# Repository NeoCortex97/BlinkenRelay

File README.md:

# BlinkenRelay
A project to have cheap and simple control over 24V Outputs

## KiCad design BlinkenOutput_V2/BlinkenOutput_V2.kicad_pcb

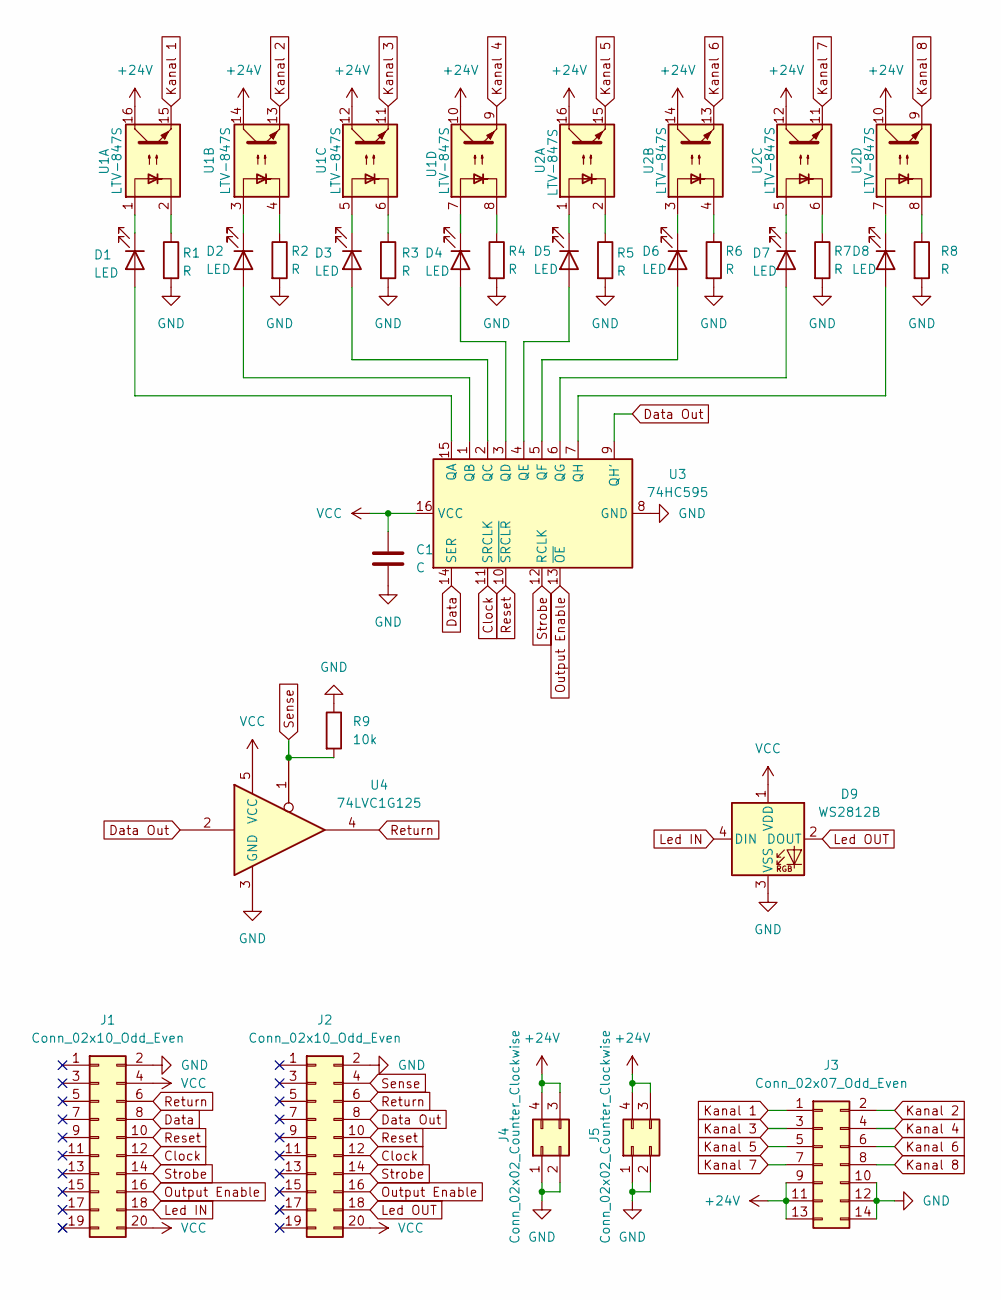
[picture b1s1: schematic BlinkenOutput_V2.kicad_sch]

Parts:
C1: C; C_0805_2012Metric_Pad1.18x1.45mm_HandSolder
D1, D2, D3, D4, D5, D6, D7, D8: LED; LED_0805_2012Metric_Pad1.15x1.40mm_HandSolder
D9: WS2812B; LED_WS2812B_PLCC4_5.0x5.0mm_P3.2mm
J1: Conn_02x10_Odd_Even; PinSocket_2x10_P2.54mm_Vertical_SMD
J2: Conn_02x10_Odd_Even; PinHeader_2x10_P2.54mm_Vertical_SMD
J3: Conn_02x07_Odd_Even; IDC-Header_2x07_P2.54mm_Horizontal
J4: Conn_02x02_Counter_Clockwise; PinHeader_2x02_P2.54mm_Vertical_SMD
J5: Conn_02x02_Counter_Clockwise; PinSocket_2x02_P2.54mm_Vertical_SMD
R1, R2, R3, R4, R5, R6, R7, R8: R; R_0805_2012Metric_Pad1.20x1.40mm_HandSolder
R9: 10k; R_0805_2012Metric_Pad1.20x1.40mm_HandSolder
U1, U2: LTV-847S; SMDIP-16_W9.53mm
U3: 74HC595; SO-16_3.9x9.9mm_P1.27mm
U4: 74LVC1G125; SOT-23-5_HandSoldering

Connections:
+24V: J3.9, J3.11, J3.13, J4.3, J4.4, J5.3, J5.4, U1.10, U1.12, U1.14, U1.16, U2.10, U2.12, U2.14, U2.16
Clock: J1.12, J2.12, U3.11 (SRCLK)
Data: J1.8, U3.14 (SER)
Data Out: J2.8, U3.9 (QH'), U4.2
GND: C1.2, D9.3 (VSS), J1.2, J2.2, J3.10, J3.12, J3.14, J4.1, J4.2, J5.1, J5.2, R1.2, R2.2, R3.2, R4.2, R5.2, R6.2, R7.2, R8.2, R9.1, U3.8 (GND), U4.3 (GND)
Kanal 1: J3.1, U1.15
Kanal 2: J3.2, U1.13
Kanal 3: J3.3, U1.11
Kanal 4: J3.4, U1.9
Kanal 5: J3.5, U2.15
Kanal 6: J3.6, U2.13
Kanal 7: J3.7, U2.11
Kanal 8: J3.8, U2.9
Led IN: D9.4 (DIN), J1.18
Led OUT: D9.2 (DOUT), J2.18
unnamed: D1.2 (A), U3.15 (QA)
unnamed: D1.1 (K), U1.1
unnamed: D2.2 (A), U3.1 (QB)
unnamed: D2.1 (K), U1.3
unnamed: D3.2 (A), U3.2 (QC)
unnamed: D3.1 (K), U1.5
unnamed: D4.2 (A), U3.3 (QD)
unnamed: D4.1 (K), U1.7
unnamed: D5.2 (A), U3.4 (QE)
unnamed: D5.1 (K), U2.1
unnamed: D6.2 (A), U3.5 (QF)
unnamed: D6.1 (K), U2.3
unnamed: D7.2 (A), U3.6 (QG)
unnamed: D7.1 (K), U2.5
unnamed: D8.2 (A), U3.7 (QH)
unnamed: D8.1 (K), U2.7
unnamed: R1.1, U1.2
unnamed: R2.1, U1.4
unnamed: R3.1, U1.6
unnamed: R4.1, U1.8
unnamed: R5.1, U2.2
unnamed: R6.1, U2.4
unnamed: R7.1, U2.6
unnamed: R8.1, U2.8
Output Enable: J1.16, J2.16, U3.13 (~OE)
Reset: J1.10, J2.10, U3.10 (~SRCLR)
Return: J1.6, J2.6, U4.4
Sense: J2.4, R9.2, U4.1
Strobe: J1.14, J2.14, U3.12 (RCLK)
VCC: C1.1, D9.1 (VDD), J1.4, J1.20, J2.20, U3.16 (VCC), U4.5 (VCC)

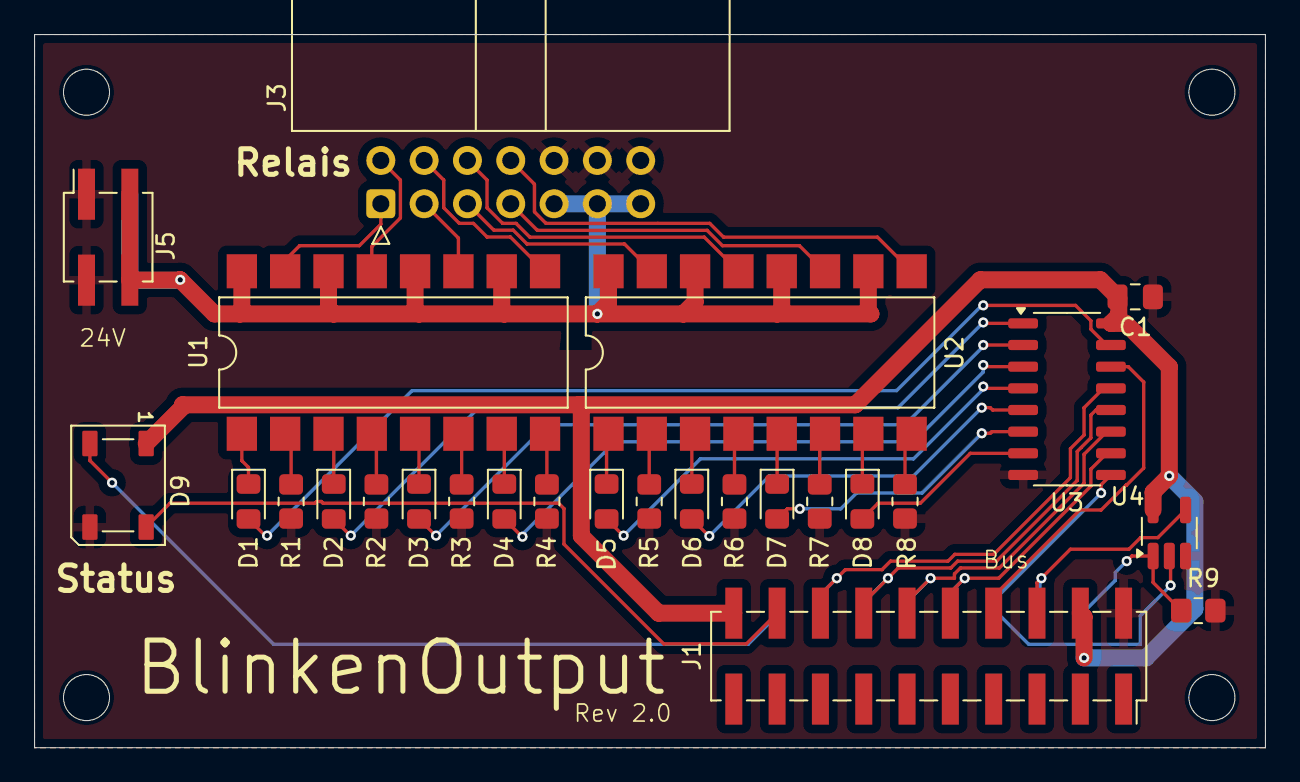
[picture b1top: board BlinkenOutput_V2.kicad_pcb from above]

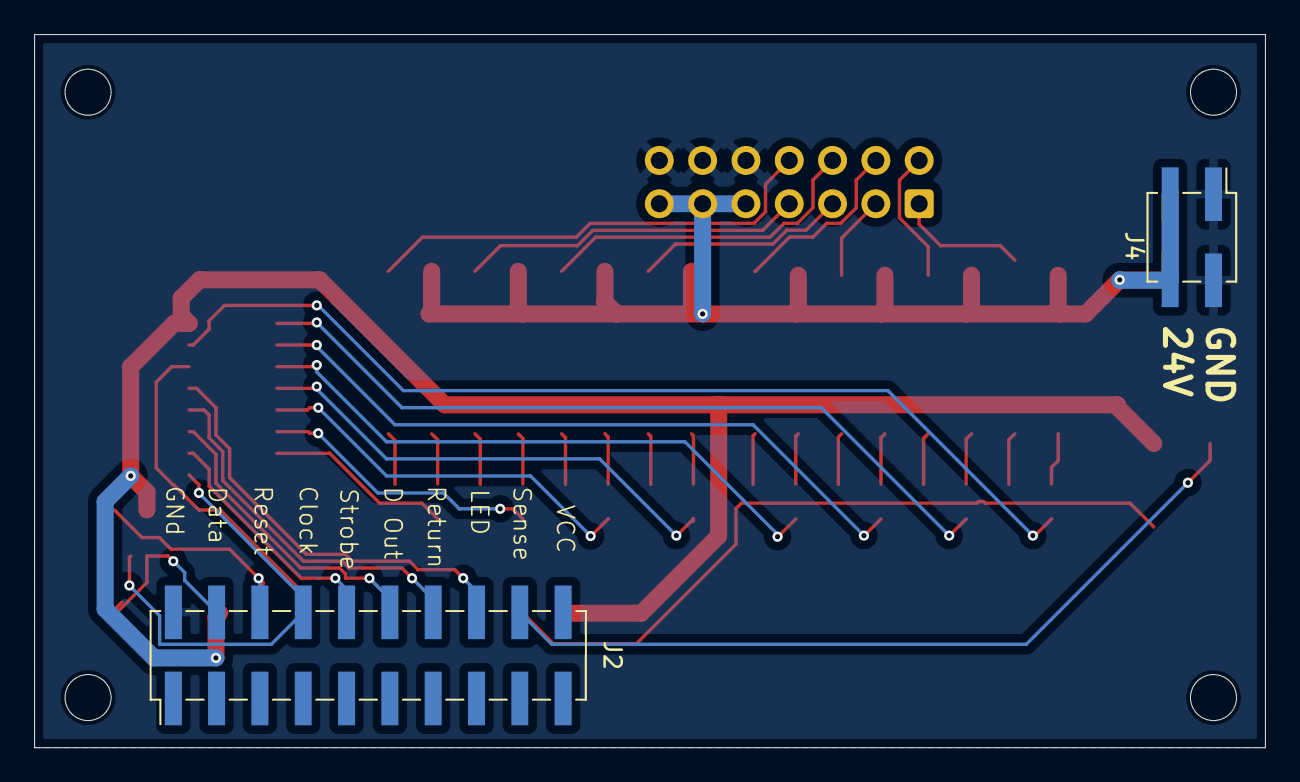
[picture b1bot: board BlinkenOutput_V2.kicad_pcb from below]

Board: 2 copper layers, 72.2 x 41.8 mm, 28 parts (2 on the bottom side), 45 nets.

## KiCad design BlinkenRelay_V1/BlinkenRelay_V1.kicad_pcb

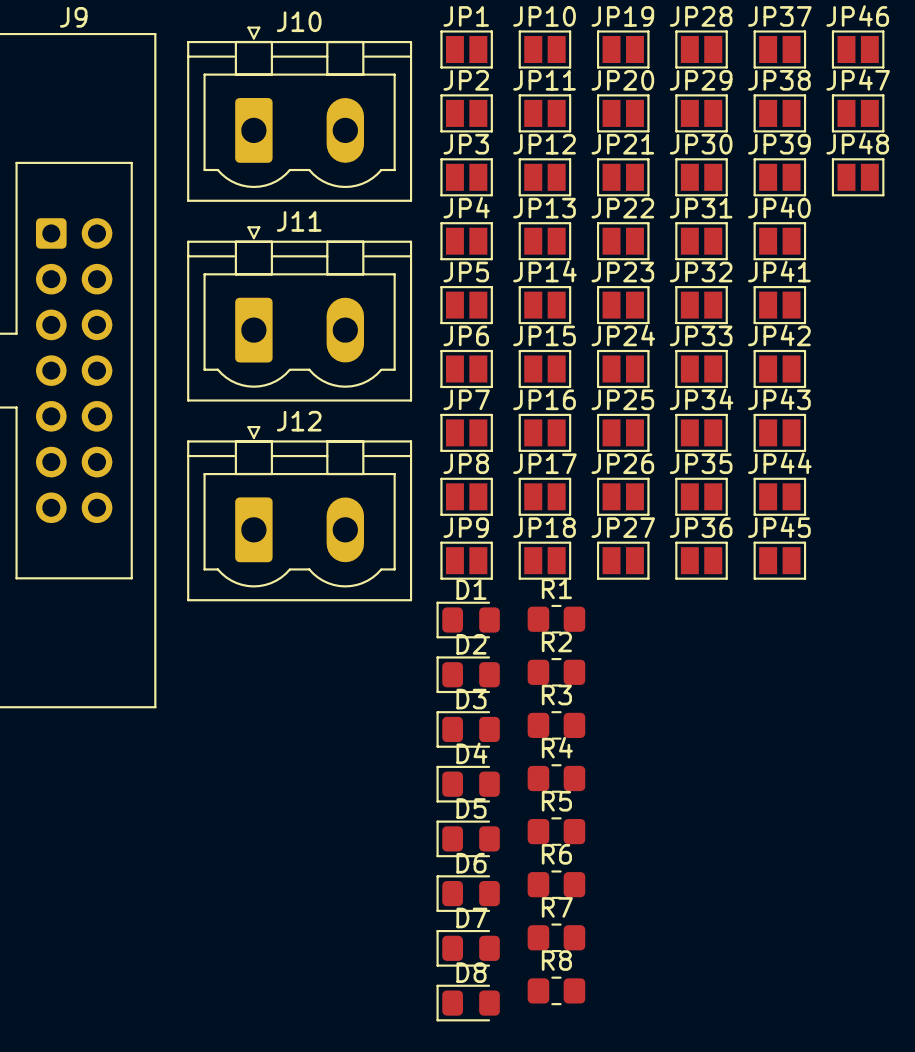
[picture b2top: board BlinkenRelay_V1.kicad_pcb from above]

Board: 2 copper layers, 68 parts (0 on the bottom side), 44 nets, no tracks yet.

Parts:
D1, D2, D3, D4, D5, D6, D7, D8: LED Low current; LED_0805_2012Metric_Pad1.15x1.40mm_HandSolder
J9: Conn_02x07_Odd_Even; IDC-Header_2x07_P2.54mm_Latch_Vertical
J10, J11, J12: Conn_01x02_Socket; PhoenixContact_MSTBVA_2,5_2-G-5,08_1x02_P5.08mm_Vertical
JP1, JP2, JP3, JP4, JP5, JP6, JP7, JP8, JP9, JP10, JP11, JP12, JP13, JP14, JP15, JP16, JP17, JP18, JP19, JP20, JP21, JP22, JP23, JP24, JP25, JP26, JP27, JP28, JP29, JP30, JP31, JP32, JP33, JP34, JP35, JP36, JP37, JP38, JP39, JP40, JP41, JP42, JP43, JP44, JP45, JP46, JP47, JP48: Jumper_2_Open; SolderJumper-2_P1.3mm_Open_Pad1.0x1.5mm
R1, R2, R3, R4, R5, R6, R7, R8: 12.1k; R_0805_2012Metric_Pad1.20x1.40mm_HandSolder

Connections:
+24V: J9.9, J9.11, J9.13, J10.1
GND: J9.10, J9.12, J9.14, J10.2, R1.2, R2.2, R3.2, R4.2, R5.2, R6.2, R7.2, R8.2
K1_COM: JP1.2 (B), JP2.2 (B)
K1_NC: JP5.2 (B), JP6.2 (B)
K1_NO: JP3.2 (B), JP4.2 (B)
K2_COM: JP7.2 (B), JP8.2 (B)
K2_NC: JP10.2 (B), JP12.2 (B)
K2_NO: JP9.2 (B), JP11.2 (B)
K3_COM: JP13.2 (B), JP14.2 (B)
K3_NC: JP16.2 (B), JP18.2 (B)
K3_NO: JP15.2 (B), JP17.2 (B)
K4_COM: JP19.2 (B), JP20.2 (B)
K4_NC: JP22.2 (B), JP24.2 (B)
K4_NO: JP21.2 (B), JP23.2 (B)
K5_COM: JP25.2 (B), JP26.2 (B)
K5_NC: JP28.2 (B), JP30.2 (B)
K5_NO: JP27.2 (B), JP29.2 (B)
K6_COM: JP31.2 (B), JP32.2 (B)
K6_NC: JP34.2 (B), JP36.2 (B)
K6_NO: JP33.2 (B), JP35.2 (B)
K7_COM: JP37.2 (B), JP38.2 (B)
K7_NC: JP40.2 (B), JP42.2 (B)
K7_NO: JP39.2 (B), JP41.2 (B)
K8_COM: JP43.2 (B), JP44.2 (B)
K8_NC: JP46.2 (B), JP48.2 (B)
K8_NO: JP45.2 (B), JP47.2 (B)
Kanal 1: D1.1 (K), J9.1
Kanal 2: D2.1 (K), J9.2
Kanal 3: D3.1 (K), J9.3
Kanal 4: D4.1 (K), J9.4
Kanal 5: D5.1 (K), J9.5
Kanal 6: D6.1 (K), J9.6
Kanal 7: D7.1 (K), J9.7
Kanal 8: D8.1 (K), J9.8
unnamed: D1.2 (A), R1.1
unnamed: D2.2 (A), R2.1
unnamed: D3.2 (A), R3.1
unnamed: D4.2 (A), R4.1
unnamed: D5.2 (A), R5.1
unnamed: D6.2 (A), R6.1
unnamed: D7.2 (A), R7.1
unnamed: D8.2 (A), R8.1
Rail A: J11.1, J12.1, JP2.1 (A), JP3.1 (A), JP5.1 (A), JP7.1 (A), JP9.1 (A), JP10.1 (A), JP13.1 (A), JP15.1 (A), JP16.1 (A), JP19.1 (A), JP21.1 (A), JP22.1 (A), JP25.1 (A), JP27.1 (A), JP28.1 (A), JP31.1 (A), JP33.1 (A), JP34.1 (A), JP37.1 (A), JP39.1 (A), JP40.1 (A), JP43.1 (A), JP45.1 (A), JP46.1 (A)
Rail B: J11.2, J12.2, JP1.1 (A), JP4.1 (A), JP6.1 (A), JP8.1 (A), JP11.1 (A), JP12.1 (A), JP14.1 (A), JP17.1 (A), JP18.1 (A), JP20.1 (A), JP23.1 (A), JP24.1 (A), JP26.1 (A), JP29.1 (A), JP30.1 (A), JP32.1 (A), JP35.1 (A), JP36.1 (A), JP38.1 (A), JP41.1 (A), JP42.1 (A), JP44.1 (A), JP47.1 (A), JP48.1 (A)

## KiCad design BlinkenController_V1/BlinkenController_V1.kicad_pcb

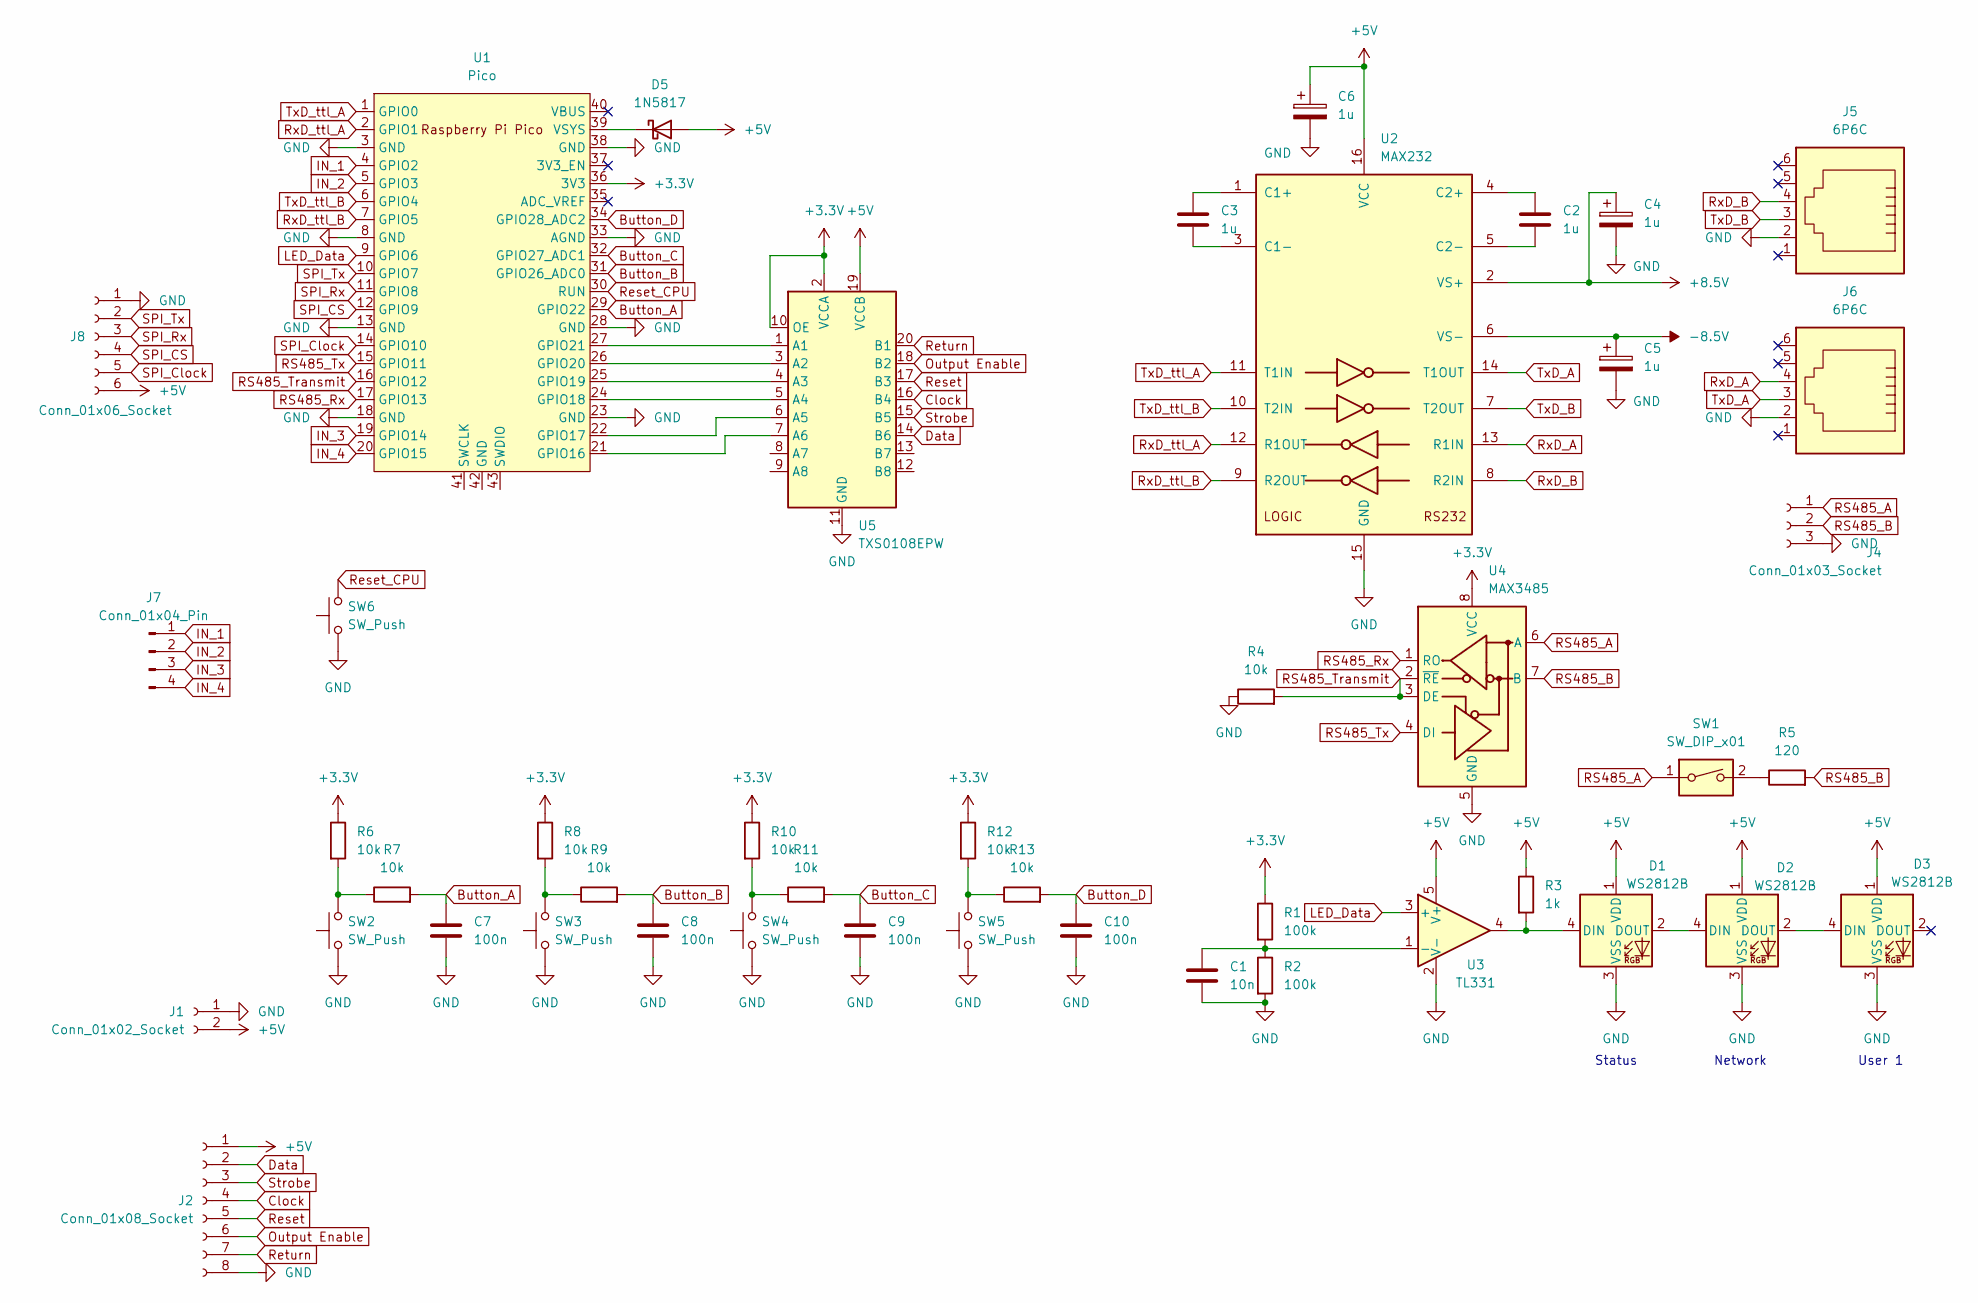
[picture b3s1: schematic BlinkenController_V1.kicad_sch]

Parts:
C1: 10n; C_0805_2012Metric_Pad1.18x1.45mm_HandSolder
C2, C3: 1u; C_Disc_D5.0mm_W2.5mm_P5.00mm
C4, C5, C6: 1u; C_Radial_D6.3mm_H5.0mm_P2.50mm
C7, C8, C9, C10: 100n; C_0805_2012Metric_Pad1.18x1.45mm_HandSolder
D1, D2, D3: WS2812B; LED_WS2812B_PLCC4_5.0x5.0mm_P3.2mm
D5: 1N5817; D_DO-41_SOD81_P10.16mm_Horizontal
J1: Conn_01x02_Socket; PhoenixContact_MSTBVA_2,5_2-G_1x02_P5.00mm_Vertical
J2: Conn_01x08_Socket; PinSocket_1x08_P2.54mm_Horizontal
J4: Conn_01x03_Socket; PhoenixContact_MSTBVA_2,5_3-G_1x03_P5.00mm_Vertical
J5, J6: 6P6C; RJ12_Amphenol_54601-x06_Horizontal
J7: Conn_01x04_Pin; PhoenixContact_MSTBVA_2,5_4-G_1x04_P5.00mm_Vertical
J8: Conn_01x06_Socket; PinSocket_1x06_P2.54mm_Vertical
R1, R2: 100k; R_0805_2012Metric_Pad1.20x1.40mm_HandSolder
R3: 1k; R_0805_2012Metric_Pad1.20x1.40mm_HandSolder
R4, R6, R7, R8, R9, R10, R11, R12, R13: 10k; R_0805_2012Metric_Pad1.20x1.40mm_HandSolder
R5: 120; R_0805_2012Metric_Pad1.20x1.40mm_HandSolder
SW1: SW_DIP_x01; SW_Slide-03_Wuerth-WS-SLTV_10x2.5x6.4_P2.54mm
SW2, SW3, SW4, SW5, SW6: SW_Push; SW_Tactile_SPST_NO_Straight_CK_PTS636Sx25SMTRLFS
U1: Pico; RaspberryPi_Pico_W_SMD
U2: MAX232; DIP-16_W7.62mm_LongPads
U3: TL331; SOT-23-5
U4: MAX3485; SOIC-8_3.9x4.9mm_P1.27mm
U5: TXS0108EPW; TSSOP-20_4.4x6.5mm_P0.65mm

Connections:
+3.3V: R1.1, R6.1, R8.1, R10.1, R12.1, U1.36 (3V3), U4.8 (VCC), U5.2 (VCCA), U5.10 (OE)
+5V: C6.1, D1.1 (VDD), D2.1 (VDD), D3.1 (VDD), D5.2 (A), J1.2, J2.1, J8.6, R3.1, U2.16 (VCC), U3.5 (V+), U5.19 (VCCB)
+8.5V: C4.1, U2.2 (VS+)
-8.5V: C5.1, U2.6 (VS-)
Button_A: C7.1, R7.2, U1.29 (GPIO22)
Button_B: C8.1, R9.2, U1.31 (GPIO26_ADC0)
Button_C: C9.1, R11.2, U1.32 (GPIO27_ADC1)
Button_D: C10.1, R13.2, U1.34 (GPIO28_ADC2)
Clock: J2.4, U1.24 (GPIO18), U5.5 (A4), U5.16 (B4)
Data: J2.2, U1.21 (GPIO16), U5.7 (A6), U5.14 (B6)
GND: C1.2, C4.2, C5.2, C6.2, C7.2, C8.2, C9.2, C10.2, D1.3 (VSS), D2.3 (VSS), D3.3 (VSS), J1.1, J2.8, J4.3, J5.2, J6.2, J8.1, R2.2, R4.1, SW2.1, SW3.1, SW4.1, SW5.1, SW6.1, U1.3 (GND), U1.8 (GND), U1.13 (GND), U1.18 (GND), U1.23 (GND), U1.28 (GND), U1.33 (AGND), U1.38 (GND), U2.15 (GND), U3.2 (V-), U4.5 (GND), U5.11 (GND)
IN_1: J7.1, U1.4 (GPIO2)
IN_2: J7.2, U1.5 (GPIO3)
IN_3: J7.3, U1.19 (GPIO14)
IN_4: J7.4, U1.20 (GPIO15)
LED_Data: U1.9 (GPIO6), U3.3 (+)
unnamed: D1.4 (DIN), R3.2, U3.4
unnamed: D1.2 (DOUT), D2.4 (DIN)
unnamed: D2.2 (DOUT), D3.4 (DIN)
unnamed: D5.1 (K), U1.39 (VSYS)
unnamed: R5.1, SW1.2
unnamed: R6.2, R7.1, SW2.2
unnamed: R8.2, R9.1, SW3.2
unnamed: R10.2, R11.1, SW4.2
unnamed: R12.2, R13.1, SW5.2
unnamed: C3.1, U2.1 (C1+)
unnamed: C3.2, U2.3 (C1-)
unnamed: C2.1, U2.4 (C2+)
unnamed: C2.2, U2.5 (C2-)
unnamed: C1.1, R1.2, R2.1, U3.1 (-)
Output Enable: J2.6, U1.26 (GPIO20), U5.3 (A2), U5.18 (B2)
RS485_A: J4.1, SW1.1, U4.6 (A)
RS485_B: J4.2, R5.2, U4.7 (B)
RS485_Rx: U1.17 (GPIO13), U4.1 (RO)
RS485_Transmit: R4.2, U1.16 (GPIO12), U4.2 (~RE), U4.3 (DE)
RS485_Tx: U1.15 (GPIO11), U4.4 (DI)
Reset: J2.5, U1.25 (GPIO19), U5.4 (A3), U5.17 (B3)
Reset_CPU: SW6.2, U1.30 (RUN)
Return: J2.7, U1.27 (GPIO21), U5.1 (A1), U5.20 (B1)
RxD_A: J6.4, U2.13 (R1IN)
RxD_B: J5.4, U2.8 (R2IN)
RxD_ttl_A: U1.2 (GPIO1), U2.12 (R1OUT)
RxD_ttl_B: U1.7 (GPIO5), U2.9 (R2OUT)
SPI_CS: J8.4, U1.12 (GPIO9)
SPI_Clock: J8.5, U1.14 (GPIO10)
SPI_Rx: J8.3, U1.11 (GPIO8)
SPI_Tx: J8.2, U1.10 (GPIO7)
Strobe: J2.3, U1.22 (GPIO17), U5.6 (A5), U5.15 (B5)
TxD_A: J6.3, U2.14 (T1OUT)
TxD_B: J5.3, U2.7 (T2OUT)
TxD_ttl_A: U1.1 (GPIO0), U2.11 (T1IN)
TxD_ttl_B: U1.6 (GPIO4), U2.10 (T2IN)

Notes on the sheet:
Network
User 1
Status

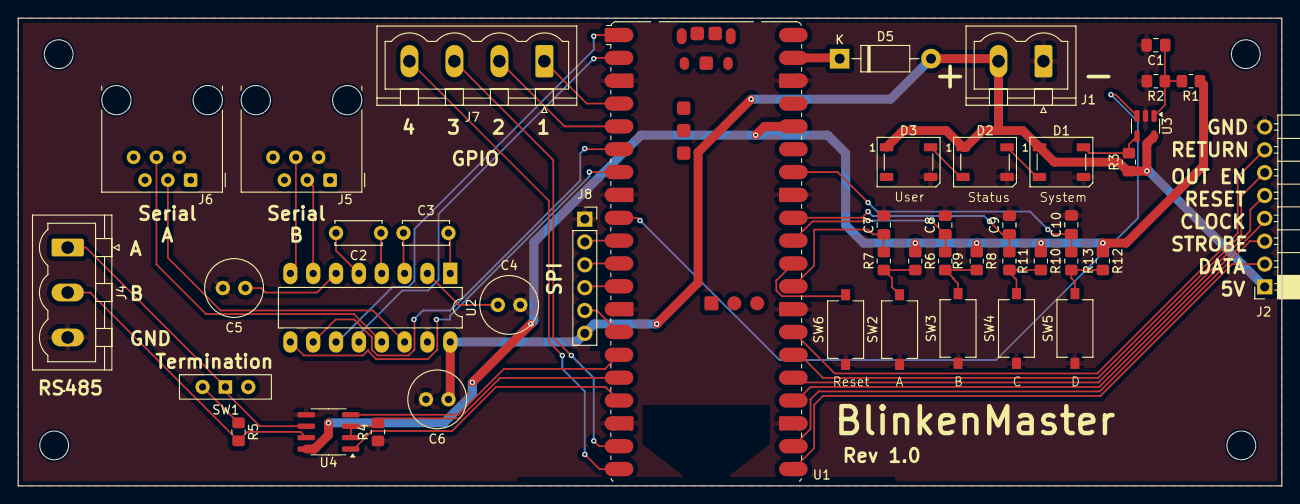
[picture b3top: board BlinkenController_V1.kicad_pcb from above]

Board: 2 copper layers, 140.5 x 52.0 mm, 44 parts (0 on the bottom side), 52 nets.

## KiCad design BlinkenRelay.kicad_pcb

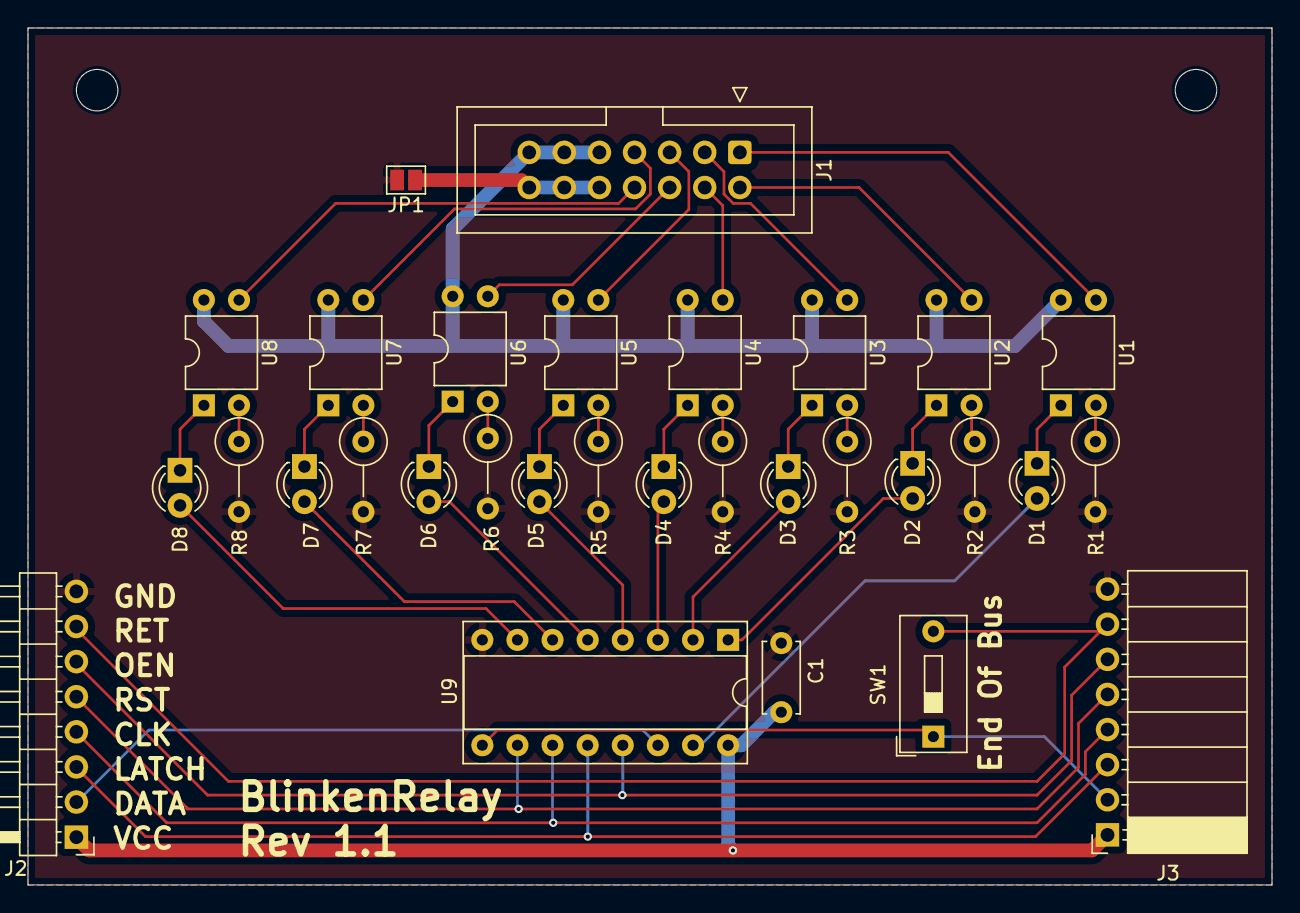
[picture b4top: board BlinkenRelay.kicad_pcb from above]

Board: 2 copper layers, 90.0 x 62.0 mm, 31 parts (0 on the bottom side), 43 nets.

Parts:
C1: 10n; C_Disc_D5.0mm_W2.5mm_P5.00mm
D1, D2, D3, D4, D5, D6, D7, D8: LED; LED_D3.0mm
J1: Conn_02x07_Odd_Even; IDC-Header_2x07_P2.54mm_Vertical
J2: Conn_01x08_Pin; PinHeader_1x08_P2.54mm_Horizontal
J3: Conn_01x08_Socket; PinSocket_1x08_P2.54mm_Horizontal
JP1: Jumper_2_Open; SolderJumper-2_P1.3mm_Open_Pad1.0x1.5mm
R1, R2, R3, R4, R5, R6, R7, R8: 140; R_Axial_DIN0309_L9.0mm_D3.2mm_P5.08mm_Vertical
SW1: SW_DIP_x01; SW_DIP_SPSTx01_Slide_9.78x4.72mm_W7.62mm_P2.54mm
U1, U2, U3, U4, U5, U6, U7, U8: LTV-817; DIP-4_W7.62mm
U9: 74HC595; DIP-16_W7.62mm_Socket

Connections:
+24V: J1.9, J1.11, J1.13, U1.4, U2.4, U3.4, U4.4, U5.4, U6.4, U7.4, U8.4
Clock: J2.4, J3.4, U9.11 (SRCLK)
Data: J2.2, U9.14 (SER)
Data Out: J3.2, SW1.1, U9.9 (QH')
GND: C1.2, J2.8, J3.8, JP1.2 (B), R1.2, R2.2, R3.2, R4.2, R5.2, R6.2, R7.2, R8.2, U9.8 (GND)
Kanal 1: J1.1, U1.3
Kanal 2: J1.2, U2.3
Kanal 3: J1.3, U3.3
Kanal 4: J1.4, U4.3
Kanal 5: J1.5, U5.3
Kanal 6: J1.6, U6.3
Kanal 7: J1.7, U7.3
Kanal 8: J1.8, U8.3
unnamed: D1.2 (A), U9.15 (QA)
unnamed: D1.1 (K), U1.1
unnamed: D2.2 (A), U9.1 (QB)
unnamed: D2.1 (K), U2.1
unnamed: D3.2 (A), U9.2 (QC)
unnamed: D3.1 (K), U3.1
unnamed: D4.2 (A), U9.3 (QD)
unnamed: D4.1 (K), U4.1
unnamed: D5.2 (A), U9.4 (QE)
unnamed: D5.1 (K), U5.1
unnamed: D6.2 (A), U9.5 (QF)
unnamed: D6.1 (K), U6.1
unnamed: D7.2 (A), U9.6 (QG)
unnamed: D7.1 (K), U7.1
unnamed: D8.2 (A), U9.7 (QH)
unnamed: D8.1 (K), U8.1
unnamed: J1.10, J1.12, J1.14, JP1.1 (A)
unnamed: R1.1, U1.2
unnamed: R2.1, U2.2
unnamed: R3.1, U3.2
unnamed: R4.1, U4.2
unnamed: R5.1, U5.2
unnamed: R6.1, U6.2
unnamed: R7.1, U7.2
unnamed: R8.1, U8.2
Output Enable: J2.6, J3.6, U9.13 (~OE)
Reset: J2.5, J3.5, U9.10 (~SRCLR)
Return: J2.7, J3.7, SW1.2
Strobe: J2.3, J3.3, U9.12 (RCLK)
VCC: C1.1, J2.1, J3.1, U9.16 (VCC)

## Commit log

2025-02-26 New revision. Fixed switched Pins.
2025-02-26 Added status LEDS and removed backups from git.
2025-02-27 Create LICENSE
2025-03-01 Relocated the base output module to nested folder and started working on generation 1 of the control board
2025-03-03 Completed board layout of controller
2025-03-07 Improved board density
2025-03-07 Renamed BlinkenRelay to BlinkenOutput
2025-03-20 Finished PCB design and added Level Shifter
2025-03-20 Overhauled the output board
